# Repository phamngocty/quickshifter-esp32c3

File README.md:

# 🏍️ Quickshifter ESP32-C3 — Hệ Thống Sang Số Nhanh Không Bóp Côn & Studio Nổ Pô

> **Quickshifter ESP32-C3** là dự án mã nguồn mở toàn diện dành cho cộng đồng xe máy Việt Nam. Hệ thống sử dụng vi điều khiển **ESP32-C3 (kiến trúc RISC-V 160MHz)** để điều khiển ngắt lửa (Ignition Cut) và ngắt kim phun (Injection Cut) theo thời gian thực với độ trễ cực thấp (< 1ms). Thiết bị tích hợp giao diện điều khiển hiện đại qua Wi-Fi Web UI, tính năng nổ pô băm xung (Popcorn Backfire), Auto RPM Limiter điều khiển bằng cần số, cân chỉnh vòng tua máy thông minh, và khóa bảo vệ mật mã Morse.

---

## 📑 Mục lục
1. [Tính năng nổi bật](#-tính-năng-nổi-bật)
2. [Sơ đồ chân & Mạch điện phần cứng](#-sơ-đồ-chân--mạch-điện-phần-cứng)
3. [Danh mục linh kiện khuyến nghị](#-danh-mục-linh-kiện-khuyến-nghị)
4. [Hướng dẫn lắp đặt cơ khí & điện trên xe](#-hướng-dẫn-lắp-đặt-cơ-khí--điện-trên-xe)
5. [Hướng dẫn nạp phần mềm (Firmware & Web UI)](#-hướng-dẫn-nạp-phần-mềm-firmware--web-ui)
6. [Hướng dẫn cấu hình & Sử dụng tính năng](#-hướng-dẫn-cấu-hình--sử-dụng-tính-năng)
   - [6.1. Kết nối Web UI](#61-kết-nối-web-ui)
   - [6.2. Cấu hình Quickshifter (Auto Map 12 dải)](#62-cấu-hình-quickshifter-auto-map-12-dải)
   - [6.3. Bật/Tắt Limiter bằng cần số (Multi-Click)](#63-bậttắt-limiter-bằng-cần-số-multi-click)
   - [6.4. Calibrate RPM (Cân chỉnh vòng tua)](#64-calibrate-rpm-cân-chỉnh-vòng-tua)
   - [6.5. Studio Bắn Bắp Rang / Nổ Pô (Popcorn Backfire)](#65-studio-bắn-bắp-rang--nổ-pô-popcorn-backfire)
   - [6.6. Khóa an toàn Morse Lock](#66-khóa-an-toàn-morse-lock)
7. [Bảng thông số tối ưu theo dòng xe](#-bảng-thông-số-tối-ưu-theo-dòng-xe)
8. [Chẩn đoán & Khắc phục sự cố (Troubleshooting)](#-chẩn-đoán--khắc-phục-sự-cố-troubleshooting)
9. [Đóng góp & Bản quyền](#-đóng-góp--bản-quyền)

---

## 🚀 Tính năng nổi bật

### 1. ⚡ Quickshifter 12 Dải Vòng Tua (Dynamic Auto-Map)
- Tự động thay đổi thời gian ngắt lửa/xăng theo từng dải 1000 RPM (từ 2000 RPM đến 14500 RPM).
- Chống khựng (bogging) ở tua thấp và chống giật/nuốt số ở tua cao.
- Tùy chọn chỉ cắt mobin lửa (IGN only) hoặc cắt cả mobin + kim phun (IGN + INJ).

### 2. 🍿 Studio Bắn Bắp Rang / Nổ Pô (Popcorn Backfire)
- **Mode 1 (Continuous)**: Cắt lửa liên tục khi đè cần số.
- **Mode 2 (Pulse Popcorn cao cấp)**: Băm xung tuần hoàn theo nhịp:
  $$\text{CUT (A: Tích xăng)} \longrightarrow \text{FIRE (B: Đốt lửa)} \longrightarrow \text{CUT (C: Ngắt nhịp)} \dots$$
  Tạo tiếng nổ giòn, đanh như xe đua MotoGP / súng máy.
- **Bảo vệ an toàn thông minh**: Ngưỡng tua tối thiểu (`manualMinRpm`, ví dụ 4000 RPM) chỉ kích hoạt khi đủ tua. Trong lúc giữ ga, chu kỳ băm xung duy trì êm ái, **tuyệt đối không ngắt ngang trả lửa đột ngột làm xe chồm lên nguy hiểm**.

### 3. 🎯 Auto RPM Limiter & Điều Khiển Bằng Cần Số
- Cắt lửa tại chỗ (Launch Limiter / Nẹt pô chống đờn ga).
- **Thao tác chân thông minh**:
  - **BẬT Limiter**: Nhấp cần số **3 cái liên tiếp (Triple-Click)** lúc dừng xe / tua máy thấp ($\le 3000\text{ RPM}$).
  - **TẮT Limiter**: Nhấp cần số **2 cái liên tiếp (Double-Click)**.
- Đồng bộ hiển thị hai chiều theo thời gian thực (SSE) lên màn hình điện thoại.

### 4. 📊 Thuật Toán Cân Chỉnh Vòng Tua (RPM Calibration Wizard)
- Tự động lấy mẫu tín hiệu vòng tua qua luồng Telemetry.
- Thuật toán lọc nhiễu cắt 10% biên (trimmed mean), tính độ lệch chuẩn (StdDev).
- Hỗ trợ cả **Cân chỉnh 1 điểm (Auto Scale)** và **Cân chỉnh 2 điểm (Scale + Offset)** khớp 100% với đồng hồ xe.

### 5. 📱 Giao Diện Web Cyberpunk Dark Mode & SoftAP Tự Động
- ESP32-C3 tự phát Wi-Fi AP riêng (`QS_tu_lam_dien_tu_xxxx`), truy cập qua địa chỉ IP `192.168.4.1`.
- Đồng hồ tua SVG mượt mà, biểu đồ Dyno Curve trực quan.
- Tự động gia hạn / đánh thức AP khi dừng xe thao tác cần số, tự tắt AP khi chạy xe để tiết kiệm năng lượng và chống nghẽn sóng.

### 6. 🔒 Khóa Chống Trộm Cần Số (Morse Lock)
- Khóa toàn bộ hệ thống đánh lửa.
- Mở khóa bằng cách gõ nhịp ngắn (dưới 300ms) và dài (trên 500ms) trên cần số (mật mã 4 ký tự).
- Chống dò mã (Spam lockout) và tự reset khi nhập sai.

### 7. 🔄 Cập Nhật OTA Không Dây & Sao Lưu Cấu Hình
- Nạp firmware mới hoặc giao diện web LittleFS trực tiếp qua trình duyệt mà không cần cắm cáp USB.
- Xuất/Nhập file cấu hình JSON chỉ với 1 click.

---

## 🔌 Sơ đồ chân & Mạch điện phần cứng

### 1. Sơ đồ nối chân vi điều khiển ESP32-C3

| Chân ESP32-C3 | Chức năng | Kiểu tín hiệu | Thiết bị kết nối |
| :--- | :--- | :--- | :--- |
| **GPIO 2** | `RPM_PIN` | Digital Input (Interrupt) | Nhận xung tua máy từ mạch cách ly Opto PC817 |
| **GPIO 4** | `SHIFT_SW` | Digital Input (Pull-up) | Cảm biến cần số (SN04-N / Microswitch / Cảm biến áp lực) |
| **GPIO 6** | `RELAY_IGN` | Digital Output | Kích Relay ngắt Mobin Sườn (IGN) |
| **GPIO 7** | `RELAY_INJ` | Digital Output | Kích Relay ngắt Kim Phun (INJ) |
| **GPIO 8** | `TEST_PWM` | PWM Output | Phát xung giả lập kiểm tra tại bàn thí nghiệm |
| **5V / VIN** | `POWER` | Nguồn vào | Nguồn DC 5V 2A từ mạch hạ áp Buck |
| **GND** | `GROUND` | Nối đất | Nối chung với Mass sườn xe |

---

### 2. Sơ đồ nguyên lý mạch tổng thể (Wiring Diagram)

```text
                  +12V Ắc Quy Sau Ổ Khóa
                            |
                 .---------------------.
                 |   Mạch Buck 12V->5V  |
                 '---------------------'
                     |             |
                   +5V DC         GND
                     |             |
        .-----------------------.  |
        |     ESP32-C3 Mini     |  |
        |                       |  |
        | GPIO 6 ---> [IN1]     |  |
        | GPIO 7 ---> [IN2]     |  |
        | GPIO 4 <--- [Black]   |  |
        | GPIO 2 <--- [Collector|  |
        '-----------------------'  |
                     |             |
                     +-------------+------------------> Mass sườn xe (GND)

=============================================================================
1. MẠCH ĐỌC VÒNG TUA (CÁCH LY QUANG OPTO PC817):
   Dây Xung Kích Mobin (ECU) ---> [Điện trở 47kΩ / 1W] ---> [Chân 1: Anode PC817]
   Mass Sườn Xe              -----------------------------> [Chân 2: Cathode PC817]
   
   Nguồn 3.3V (ESP32)        ---> [Điện trở kéo 10kΩ]  ---> [Chân 4: Collector PC817] ---> GPIO 2
   Mass ESP32                -----------------------------> [Chân 3: Emitter PC817]

=============================================================================
2. MẠCH CẢM BIẾN CẦN SỐ (SN04-N NPN Thường Mở - NO):
   Dây Nâu (Brown) ---> +12V Sau Ổ Khóa (qua cầu chì 1A)
   Dây Xanh (Blue) ---> Mass Sườn Xe (GND)
   Dây Đen (Black) ---> GPIO 4 (ESP32 đã bật trở kéo nội PULLUP hoặc lắp thêm trở 10kΩ lên 3.3V)

=============================================================================
3. MẠCH CẮT LỬA VÀ KIM PHUN (RELAY 2 KÊNH KHUYẾN NGHỊ DÙNG TIẾP ĐIỂM NC):
   - Cắt Mobin (IGN):
     Cắt đôi dây dương 12V cấp vào Mobin sườn:
     Đầu nguồn 12V tới      ---> Chân COM1 (Relay 1)
     Đầu vào cọc Mobin      ---> Chân NC1  (Relay 1 - Thường đóng)
     (Khi relay KHÔNG kích, mạch thông bình thường. Khi kích cắt, tiếp điểm mở ra ngắt lửa).

   - Cắt Kim Phun (INJ):
     Cắt đôi dây dương cấp nguồn Kim Phun:
     Đầu nguồn 12V tới      ---> Chân COM2 (Relay 2)
     Đầu vào Kim Phun       ---> Chân NC2  (Relay 2 - Thường đóng)
```

---

## 🛒 Danh mục linh kiện khuyến nghị

| Linh kiện | Thông số kỹ thuật | Ước tính chi phí |
| :--- | :--- | :--- |
| **Bo mạch điều khiển** | ESP32-C3 Super Mini (USB Type-C, Flash 4MB) | 70.000 – 90.000 VNĐ |
| **Mạch Relay** | Module Relay 2 kênh 5V Optocoupler cách ly (Chịu dòng 10A) | 40.000 – 60.000 VNĐ |
| **Cảm biến cần số** | Cảm biến tiệm cận kim loại SN04-N (NPN NO, dải áp 10-30V) | 35.000 – 50.000 VNĐ |
| **Mạch cách ly xung tua** | Optocoupler PC817 + Điện trở 47kΩ 2W + 10kΩ 1/4W | 10.000 – 15.000 VNĐ |
| **Bộ hạ áp nguồn** | Module Buck DC-DC LM2596 hoặc Mini-360 (Vào 12V ra 5V 2A ổn định) | 20.000 – 35.000 VNĐ |
| **Hộp bảo vệ & Phụ kiện** | Hộp nhựa chống nước IP65, dây điện chịu nhiệt, giắc cắm chống nước | 40.000 – 60.000 VNĐ |
| **Tổng cộng** | | **~220.000 – 310.000 VNĐ** |

---

## 🛠️ Hướng dẫn lắp đặt cơ khí & điện trên xe

### Bước 1: Lắp đặt cảm biến cần số
1. Chế pat nhôm/sắt chữ L bắt chắc chắn vào gác chân hoặc lốc máy gần cần số.
2. Căn chỉnh đầu cảm biến tiệm cận **SN04-N** cách đùi cần số hoặc ốc bắt cần số khoảng **2 – 3mm**.
3. Thử gạt/đạp cần số: Đèn LED màu đỏ trên đuôi cảm biến phải **SÁNG** khi có lực ấn sang số và **TẮT** ngay khi nhả chân về vị trí nghỉ.

### Bước 2: Lấy tín hiệu tua máy (RPM)
- **Xe Fi (Phun xăng điện tử)**: Trích dây tín hiệu kích mobin (từ ECU về Mobin sườn) đưa qua điện trở $47\text{ k}\Omega$ vào chân Anode của Opto PC817.
- **Xe xăng cơ**: Quấn 15–20 vòng dây đồng tráng men quanh dây cao áp bugi để lấy cảm ứng từ, hoặc trích xung từ cuộn kích (Pick-up coil) trên mâm lửa.

### Bước 3: Đấu nối Relay cắt Mobin / Kim phun
- Luôn sử dụng cặp tiếp điểm **COM** và **NC (Normally Closed - Thường đóng)** của Relay.
- Ưu điểm: Trong trường hợp bo mạch ESP32 bị mất nguồn hoặc gặp sự cố, tiếp điểm NC vẫn luôn đóng kín, xe vẫn nổ máy và di chuyển bình thường như xe zin, không lo nằm đường!

---

## 💻 Hướng dẫn nạp phần mềm (Firmware & Web UI)

Dự án được xây dựng bằng **PlatformIO** trên nền tảng Arduino Framework cho ESP32-C3.

### 1. Chuẩn bị môi trường
1. Cài đặt [Visual Studio Code](https://code.visualstudio.com/).
2. Cài đặt Extension **PlatformIO IDE** trong VS Code.
3. Tải mã nguồn dự án:
   ```bash
   git clone https://github.com/your-username/quickshifter-esp32c3.git
   cd quickshifter-esp32c3
   ```

### 2. Nạp chương trình vào bo mạch
Kết nối bo ESP32-C3 vào máy tính qua cáp Type-C chất lượng tốt (có truyền dữ liệu):

```powershell
# 1. Biên dịch và nạp Firmware
platformio run -e esp32-c3-dev -t upload

# 2. Đóng gói và nạp Giao diện Web (LittleFS)
platformio run -e esp32-c3-dev -t uploadfs
```

*(Nếu dùng PlatformIO trên Windows cài sẵn môi trường người dùng, có thể chạy lệnh qua đường dẫn đầy đủ `& "$env:USERPROFILE\.platformio\penv\Scripts\platformio.exe" run -e esp32-c3-dev -t upload`).*

---

## 📖 Hướng dẫn cấu hình & Sử dụng tính năng

### 6.1. Kết nối Web UI
1. Bật khóa xe máy để cấp điện cho mạch.
2. Dùng điện thoại tìm kiếm mạng Wi-Fi:
   - **Tên Wi-Fi (SSID)**: `QS_tu_lam_dien_tu_XXXXXX` *(XXXXXX là 6 ký tự MAC riêng của chip)*.
   - **Mật khẩu**: Mặc định để trống (Open Network). Có thể cài mật khẩu bảo mật trong tab Cấu hình.
3. Mở trình duyệt web (Chrome / Safari), truy cập địa chỉ IP:
   ```text
   http://192.168.4.1
   ```

---

### 6.2. Cấu hình Quickshifter (Auto Map 12 dải)
Vào tab **Sang Số (Shift & Cut)**:
- **Thời gian cắt cố định (Fixed Cut)**: Dùng khi tắt Auto Map (khuyến nghị 65–80ms).
- **Auto Map (12 dải tua)**: Tự động điều chỉnh thời gian cắt từ thấp đến cao:
  - Dải tua thấp (2,000 – 5,000 RPM): Cần thời gian cắt dài hơn (**105 – 135ms**) do cốt số quay chậm.
  - Dải tua trung bình (5,000 – 9,000 RPM): Thời gian cắt vừa phải (**85 – 105ms**).
  - Dải tua cao (9,000 – 14,500 RPM): Thời gian cắt cực nhanh (**60 – 75ms**) để tối đa gia tốc.

---

### 6.3. Bật/Tắt Limiter bằng cần số (Multi-Click)
Không cần phải móc điện thoại ra khi đang chạy xe, bạn có thể điều khiển Auto RPM Limiter trực tiếp bằng chân:
- **Kích hoạt BẬT**: Khi xe đang dừng nổ máy garanti hoặc tua máy thấp ($\le 3000\text{ RPM}$), dùng mũi chân nhấp cần số **3 cái dứt khoát liên tiếp (Triple-Click)** trong vòng 0.8 giây. Còi/Relay sẽ báo nhận lệnh và Limiter chuyển sang `ACTIVE`.
- **Hủy TẮT**: Nhấp cần số **2 cái liên tiếp (Double-Click)**. Limiter chuyển về `OFF`.
- Khi tua máy đang kéo ga cao ($> 3000\text{ RPM}$), mọi thao tác đạp cần số đều ưu tiên 100% cho việc sang số Quickshifter, không bao giờ bị nhầm lệnh.

---

### 6.4. Calibrate RPM (Cân chỉnh vòng tua)
Vào tab **Hệ Thống (System)** $\rightarrow$ mục **Calibrate RPM**:
1. **Calibrate 1 điểm**:
   - Nhìn đồng hồ xe, giữ đều ga ở 1 mức cố định (ví dụ 5,000 RPM).
   - Nhập `5000` vào ô **Target RPM**.
   - Bấm nút **Calibrate (auto)**.
   - Hệ thống sẽ tự động đo 12 mẫu liên tiếp, lọc nhiễu và tính toán hệ số nhân `Scale Factor` chuẩn xác nhất nạp vào xe.
2. **Calibrate 2 điểm**:
   - Bước 1: Giữ ga thấp (ví dụ 2,500 RPM) $\rightarrow$ bấm lấy mẫu điểm Thấp.
   - Bước 2: Giữ ga cao (ví dụ 7,000 RPM) $\rightarrow$ bấm lấy mẫu điểm Cao.
   - Bấm **Calibrate 2 điểm** để thuật toán tuyến tính hóa tính đồng thời cả `Scale Factor` và `Offset RPM`.

---

### 6.5. Studio Bắn Bắp Rang / Nổ Pô (Popcorn Backfire)
Vào tab **Nổ Pô (Backfire)**:
- Bật công tắc **Manual Backfire**.
- Chọn chế độ **Mode 2: Băm Xung (Pulse Popcorn)**:
  - **A (Cut Ms)**: Thời gian ngắt lửa nạp xăng vào buồng xả (mặc định 95ms).
  - **B (Fire Ms)**: Thời gian bật lửa kích nổ pháo pô (mặc định 35ms).
  - **C (Off Ms)**: Thời gian ngắt nhịp hồi lưu (mặc định 55ms).
  - **D (Repeat)**: Số tiếng nổ trong 1 chu kỳ (mặc định 4 tiếng).
  - **Min RPM**: Vòng tua tối thiểu cho phép bắn bắp rang (mặc định 4000 RPM).
- **Cách chơi**: Chạy xe lên trên 4000 RPM, giữ đều tay ga và đè chân lên cần số quá 0.6 giây. Tiếng pô sẽ bắn đôm đốp liên hồi kiểu xe đua Moto3/MotoGP. Nhả chân khỏi cần số là tiếng nổ ngưng ngay lập tức, hoàn toàn êm ái và an toàn!

---

### 6.6. Khóa an toàn Morse Lock
- Khi bật tính năng Khóa cần số: Xe sẽ bị ngắt mobin lửa liên tục, kẻ gian bẻ khóa cũng không thể nào nổ máy.
- **Mở khóa**: Nhấp cần số theo chuỗi nhịp ngắn (dưới 0.3s = số `0`) và nhịp dài (giữ trên 0.5s = số `1`). Mật mã gồm 4 ký tự (ví dụ `1001`: Dài - Ngắn - Ngắn - Dài).
- Nếu bấm nhầm, giữ cần số trên 2 giây để reset bộ nhớ đệm và gõ lại từ đầu.

---

## 🏍️ Bảng thông số tối ưu theo dòng xe

| Dòng xe | Động cơ | Vòng tua kích hoạt (Min RPM) | Thời gian cắt cố định | Thời gian băm Popcorn (A/B/C) |
| :--- | :--- | :--- | :--- | :--- |
| **Exciter 150 / 155 VVA** | 150cc SOHC 4V | 3,000 RPM | 65 ms | A: 95ms / B: 35ms / C: 55ms |
| **Winner 150 / Winner X** | 150cc DOHC 4V | 3,200 RPM | 60 ms | A: 90ms / B: 30ms / C: 50ms |
| **Raider 150 / Satria F150** | 150cc DOHC High-RPM | 3,500 RPM | 55 ms | A: 85ms / B: 30ms / C: 45ms |
| **CBR150R / Yamaha R15V3-V4** | 155cc VVA Sportbike | 3,500 RPM | 58 ms | A: 90ms / B: 35ms / C: 50ms |
| **Yamaha MT-03 / R3** | 321cc 2 Xi-lanh | 3,000 RPM | 52 ms | A: 80ms / B: 25ms / C: 40ms |

---

## 🔧 Chẩn đoán & Khắc phục sự cố (Troubleshooting)

| Hiện tượng | Nguyên nhân khả dĩ | Hướng dẫn khắc phục |
| :--- | :--- | :--- |
| **Sang số bị khựng đầu, hụt tốc độ** | Thời gian cắt (`Cut Ms`) quá dài | Giảm thời gian cắt xuống 5–10ms (ví dụ từ 80ms xuống 70ms). |
| **Sang số bị nặng chân, sượng số** | Thời gian cắt quá ngắn, nhông số chưa kịp nhả | Tăng thời gian cắt lên 5–10ms (ví dụ từ 55ms lên 65ms). |
| **Đạp cần số không thấy cắt lửa** | Cảm biến chưa bắt trúng cần số hoặc hỏng dây | Kiểm tra đèn LED sau đuôi cảm biến. Chỉnh khoảng cách về 2mm. Kiểm tra tab Telemetry xem trạng thái `Shift Sensor` có nhảy sang `PRESSED` không. |
| **Không hiển thị vòng tua trên Web** | Đấu sai dây xung tua hoặc lỏng trở Opto | Kiểm tra lại dây vào chân 1 & 2 của PC817. Kiểm tra điện trở 47kΩ. |
| **Không tìm thấy Wi-Fi của mạch** | AP tự tắt sau thời gian chờ để tiết kiệm điện | Nhấp cần số 1 cái lúc dừng xe để đánh thức Wi-Fi, hoặc tắt mở lại khóa xe. |
| **Xe chết máy khi đang chạy** | Đấu nhầm chân Relay NO thay vì NC | Phải đấu vào chân **COM** và **NC** của Relay để khi mất điện tiếp điểm vẫn đóng. |

---

## 🤝 Đóng góp & Bản quyền

- Dự án được phát hành dưới giấy phép mã nguồn mở **MIT License**.
- Mọi đóng góp, báo lỗi (Issue) hoặc đề xuất tính năng mới (Pull Request) đều được hoan nghênh nồng nhiệt!
- Thảo luận và chia sẻ kinh nghiệm lắp đặt thực tế tại các diễn đàn công nghệ và hội nhóm xe máy:
  - Diễn đàn VOZ: Thread *Quickshifter ESP32 DIY*.
  - Nhóm Facebook Biker & Kỹ thuật xe máy Việt Nam.

---

<p align="center">
  <b>Made with ❤️ by Vietnamese Bikers & Embedded Developers</b><br>
  <i>Chinh phục mọi cung đường — Tự do trong từng cú gạt số! 🏍️💨</i>
</p>

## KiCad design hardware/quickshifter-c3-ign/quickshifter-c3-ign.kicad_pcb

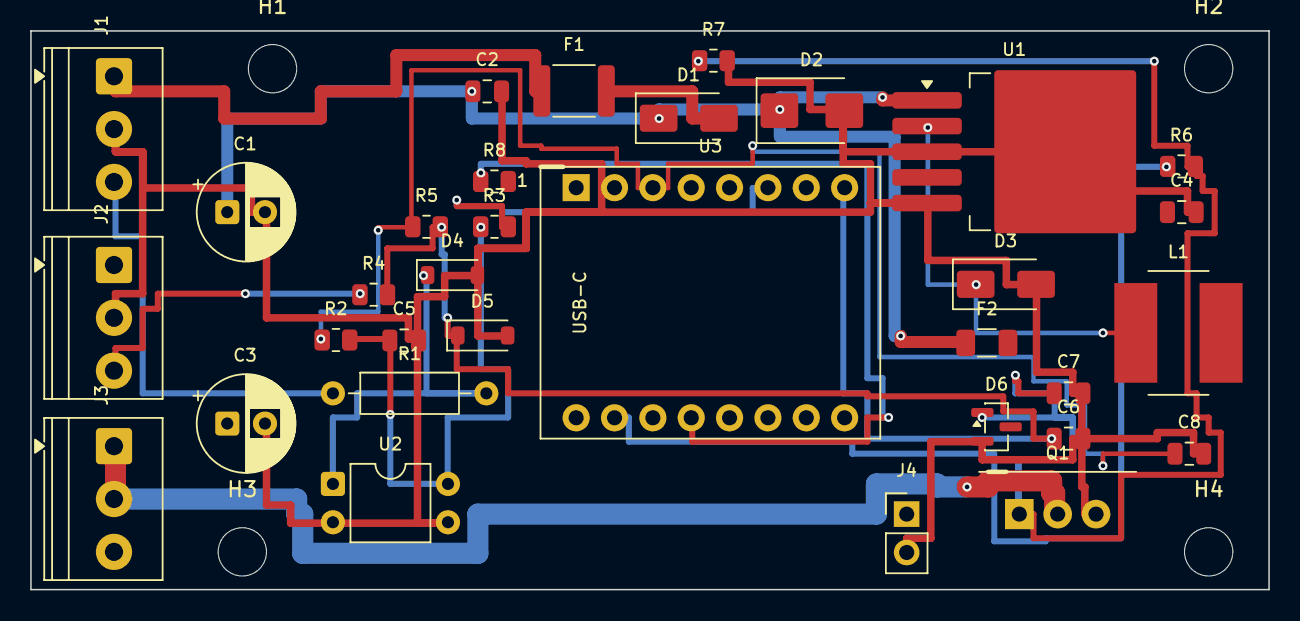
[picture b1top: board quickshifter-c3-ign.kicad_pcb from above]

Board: 2 copper layers, 82.0 x 37.0 mm, 37 parts (0 on the bottom side), 19 nets.

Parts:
C1: 100uF/25V; CP_Radial_D6.3mm_P2.50mm
C2, C4, C7, C8: 100nF; C_0805_2012Metric
C3: 220uF/16V; CP_Radial_D6.3mm_P2.50mm
C5, C6: 10nF; C_0805_2012Metric
D1, D3: SS34; D_SMA
D2: SMBJ18A; D_SMB
D4: 1N4148; D_SOD-123
D5: BZT52C5V1; D_SOD-123
D6: BZX84C15; SOT-23
F1: 1.1A; Fuse_1812_4532Metric
F2: 0.5A; Fuse_1206_3216Metric
H1, H2, H3, H4: MountingHole_3.2mm_M3
J1: BIKE 12V/GND/RPM; TerminalBlock_Phoenix_PT-1,5-3-3.5-H_1x03_P3.50mm_Horizontal
J2: SN04-N; TerminalBlock_Phoenix_PT-1,5-3-3.5-H_1x03_P3.50mm_Horizontal
J3: IGN TRIGGER CUT; TerminalBlock_Phoenix_PT-1,5-3-3.5-H_1x03_P3.50mm_Horizontal
J4: TEST_PWM; PinHeader_1x02_P2.54mm_Vertical
L1: 100uH; L_Bourns_SRN8040TA
Q1: IRGB14C40L; TO-220_Standing
R1: 4k7 0.5W; R_Axial_DIN0207_L6.3mm_D2.5mm_P10.16mm_Horizontal
R2, R5, R7: 10k; R_0805_2012Metric
R3, R8: 1k; R_0805_2012Metric
R4: 4k7; R_0805_2012Metric
R6: 100; R_0805_2012Metric
U1: LM2596S-5.0; TO-263-5_TabPin3
U2: PC817; DIP-4_W7.62mm
U3: ESP32-C3-SuperMini

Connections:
+3V3: C8.1, R2.1, R5.1, U3.3
+5V: C3.1, C4.1, L1.2, U1.4, U3.1
+12V_F: D1.2, F1.2
+12V_IN: F1.1, J1.1
+12V_P: C1.1, C2.1, D1.1, D2.1, F2.1, U1.1
+12V_SENS: F2.2, J2.1
GND: C1.2, C2.2, C3.2, C4.2, C5.2, C6.2, C7.2, C8.2, D2.2, D3.2, D4.2, D5.2, D6.2, J1.2, J2.2, J4.2, Q1.3, R7.2, U1.3, U1.5, U2.2, U2.3, U3.2
IGBT_G: C7.1, D6.1, Q1.1, R6.2, R7.1
IGN_DRV: R6.1, U3.10
RPM_IN: J1.3, R1.1
RPM_LED_A: D4.1, R1.2, U2.1
RPM_OPT: C5.1, R2.2, R3.1, U2.4
RPM_SIG: R3.2, U3.6
SHIFT_IN: J2.3, R4.1
SHIFT_SIG: C6.1, D5.1, R4.2, R5.2, U3.8
SW_NODE: D3.1, L1.1, U1.2
TEST_PWM: R8.1, U3.12
TEST_PWM_OUT: J4.1, R8.2
TRIG: J3.1, J3.2, Q1.2

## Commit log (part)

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2026-01-06 Init
2026-01-08 tạo init
2026-01-09 thêm backfrire manual v1 chưa test
2026-01-09 Manual Init
2026-01-12 back frie manual v1 chưa test
2026-01-12 back frie chưa test
2026-01-13 sữa lưu cấu hình back frie manual
2026-01-14 sữa backfrire mode 2 chưa xong
2026-01-15 backfrie manual ok
2026-01-15 THÊM MD
2026-03-14 sữa rpm đọc xung ecu
2026-03-14 v3.1
2026-03-17 fixCác cải tiến đã thực hiện 1. Bảo vệ Quickshift ở tua thấp (Min RPM Guard) Vấn đề: Trước đây quickshift có thể kích hoạt ở bất kỳ RPM nào, dễ gây chết máy khi đi chậm. Giải pháp: Thêm Guard conditi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
2026-03-19 fomat repo
2026-03-21 fix band
2026-03-25 fixban rpm chưa test
2026-03-25 fix rpm bin
2026-05-03 fix rpm ok

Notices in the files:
README.md:
License: MIT
